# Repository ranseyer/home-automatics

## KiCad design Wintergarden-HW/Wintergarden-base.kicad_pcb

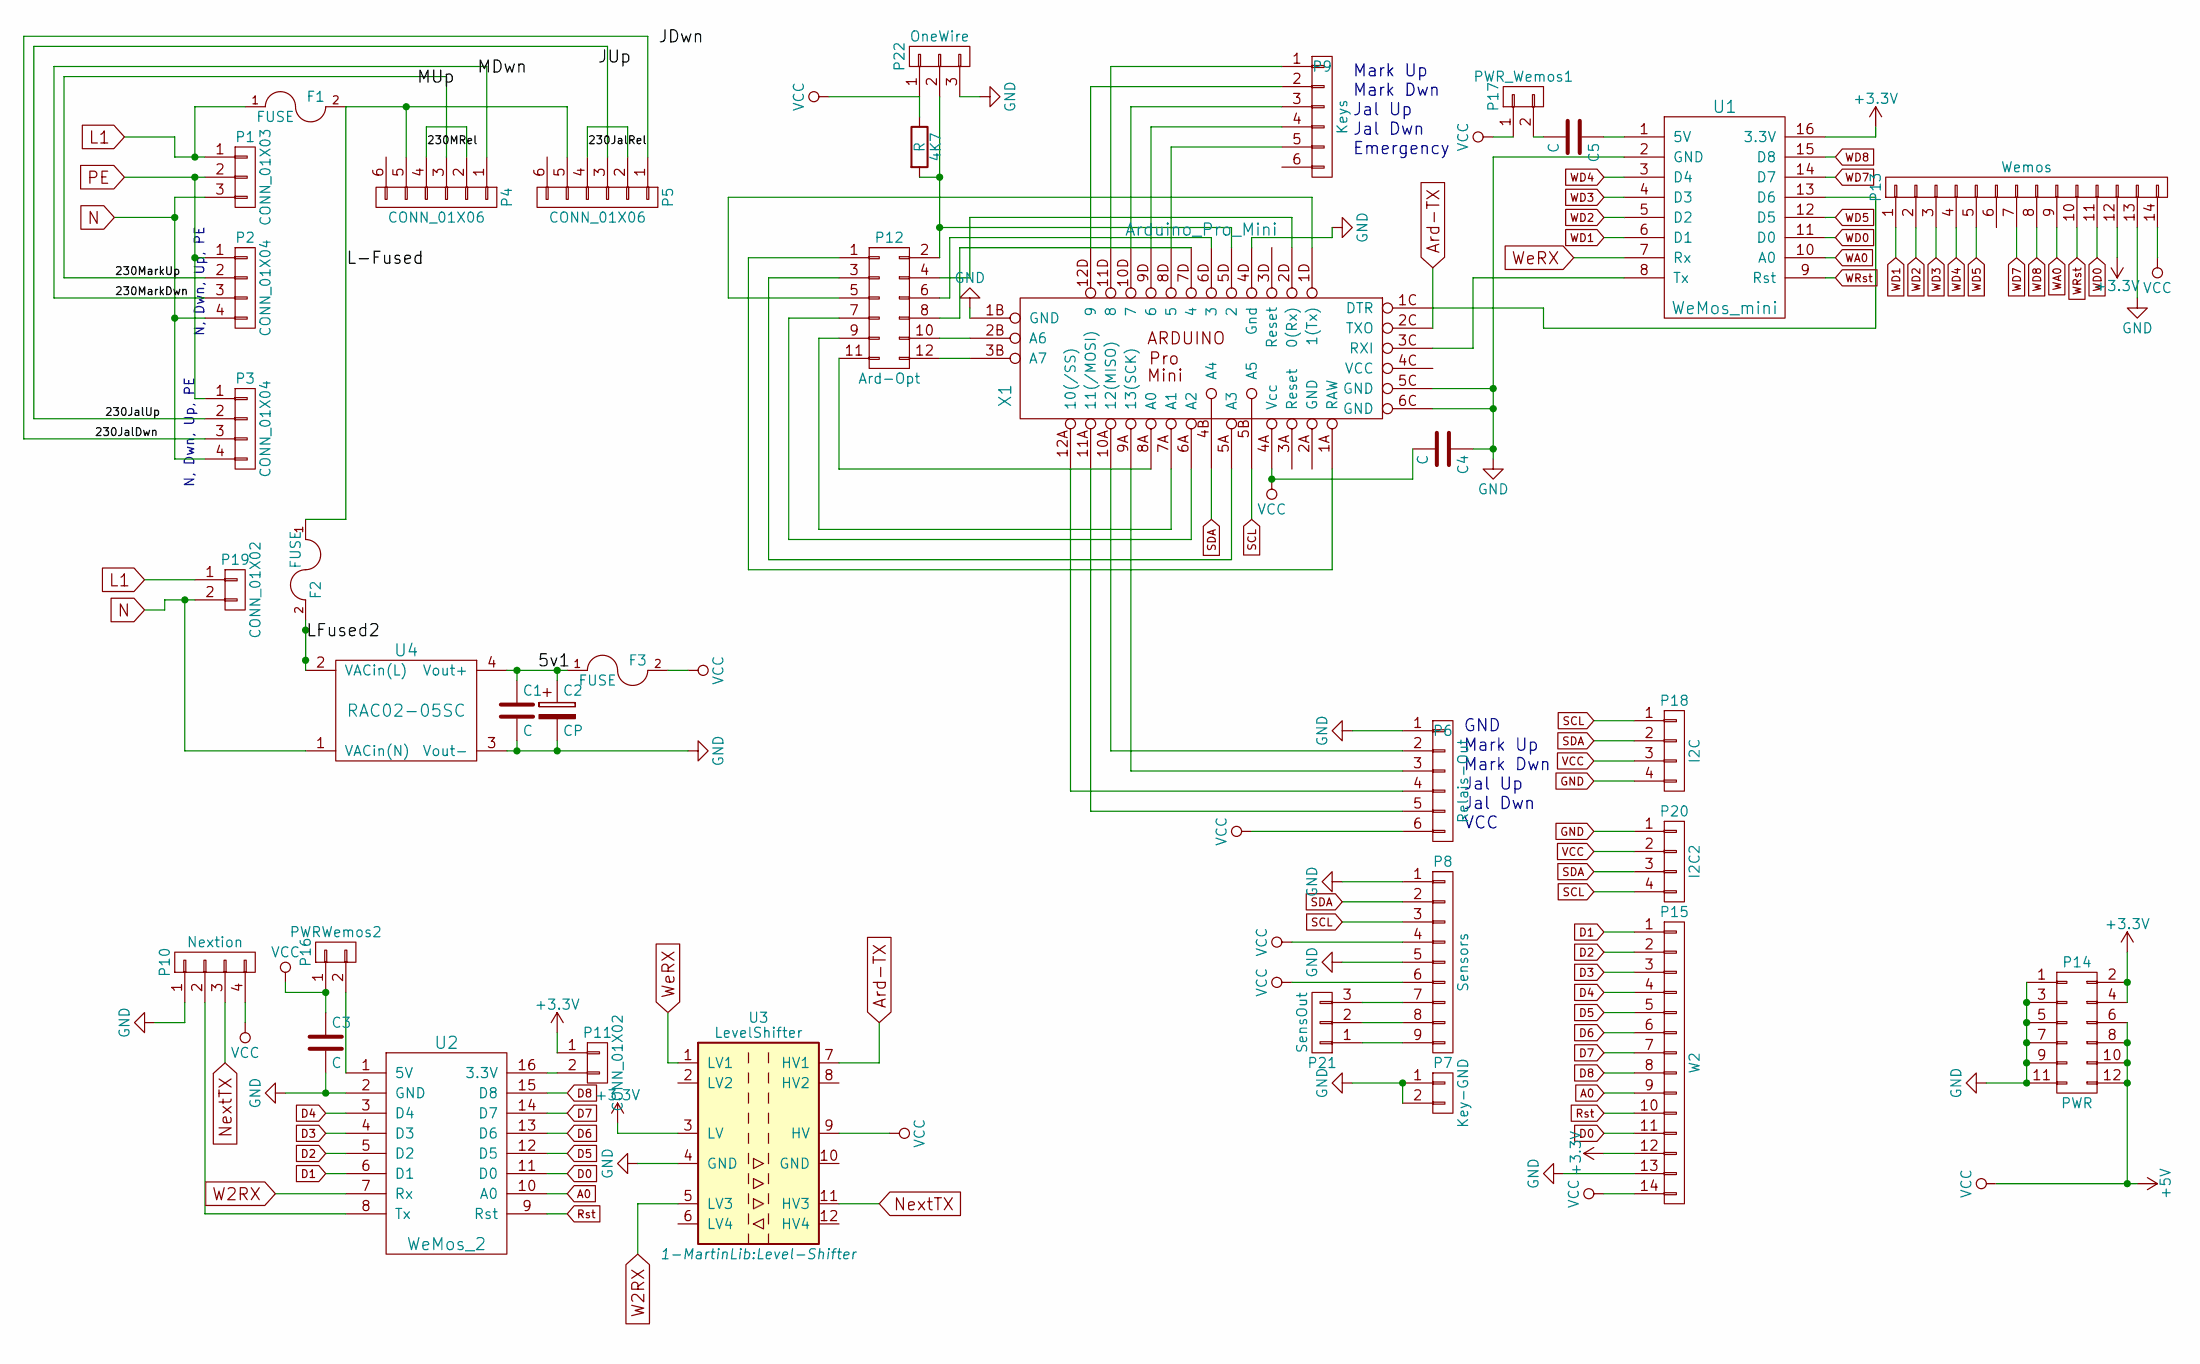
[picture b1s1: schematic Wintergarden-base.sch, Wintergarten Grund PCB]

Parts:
4K7: R; R_0805_HandSoldering
C1: C; C_0805_HandSoldering
C2: CP; C_Radial_D10_L20_P5
C3, C4, C5: C; C_1210_HandSoldering
F1, F2: FUSE; Fuseholder5x20_horiz_SemiClosed_Casing10x25mm
F3: FUSE; Fuseholder_Fuse_TR5_Littlefuse-No560_No460
P1: CONN_01X03; PhoenixContact_MSTBVA-G_03x5.00mm_Vertical
P2, P3: CONN_01X04; PhoenixContact_MSTBVA-G_04x5.00mm_Vertical
P4, P5: CONN_01X06; PhoenixContact_MSTBVA-G_06x5.00mm_Vertical
P6: Relais-Out; Pin_Header_Straight_1x06
P7: Key-GND; PhoenixContact_MSTBVA-G_02x5.00mm_Vertical
P8: Sensors; PhoenixContact_MCV-G_09x3.50mm_Vertical
P9: Keys; PhoenixContact_MCV-G_06x3.50mm_Vertical
P10: Nextion; Pin_Header_Straight_1x04
P11: CONN_01X02; Pin_Header_Straight_2x01
P12: Ard-Opt; Pin_Header_Straight_2x06
P13: Wemos; Pin_Header_Straight_2x07
P14: PWR; Pin_Header_Straight_2x06
P15: W2; Pin_Header_Straight_2x07
P16: PWRWemos2; Pin_Header_Straight_2x01
P17: PWR_Wemos1; Pin_Header_Straight_2x01
P18: I2C; Pin_Header_Straight_1x04
P19: CONN_01X02; PhoenixContact_MSTBVA-G_02x5.00mm_Vertical
P20: I2C2; Pin_Header_Straight_1x04
P21: SensOut; Pin_Header_Straight_1x03
P22: OneWire; Pin_Header_Straight_1x03
U1: WeMos_mini; D1_mini_board
U2: WeMos_2; D1_mini_board
U3: LevelShifter; Level-Shifter
U4: RAC02-05SC; HLK-PM01
X1: Arduino_Pro_Mini

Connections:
+3V3: P11.1, P13.12, P14.2, P14.4, P15.12, U1.16 (3.3V), U3.3 (LV)
/5v1: C1.1, C2.1, F3.1, U4.4 (Vout+)
/230JalDwn: P3.3, P5.1
/230JalRel: P5.2, P5.4
/230JalUp: P3.2, P5.3
/230MRel: P4.2, P4.4
/230MarkDwn: P2.3, P4.1
/230MarkUp: P2.2, P4.3
/L-Fused: F1.2, F2.1, P4.5, P5.5
/LFused2: F2.2, U4.2 (VACin(L))
A0: P15.9, U2.10 (A0)
Ard-TX: U3.7 (HV1), X1.2C (TXO)
D0: P15.11, U2.11 (D0)
D1: P15.1, U2.6 (D1)
D2: P15.2, U2.5 (D2)
D3: P15.3, U2.4 (D3)
D4: P15.4, U2.3 (D4)
D5: P15.5, U2.12 (D5)
D6: P15.6, U2.13 (D6)
D7: P15.7, U2.14 (D7)
D8: P15.8, U2.15 (D8)
GND: C1.2, C2.2, C3.2, C4.1, P6.1, P7.1, P7.2, P8.1, P8.5, P10.1, P13.13, P14.1, P14.3, P14.5, P14.7, P14.9, P14.11, P15.13, P18.4, P20.1, P22.3, U1.2 (GND), U2.2 (GND), U3.4 (GND), U4.3 (Vout-), X1.1B (GND), X1.4D (Gnd), X1.5C (GND), X1.6C (GND)
L1: F1.1, P1.1, P19.1
N: P1.3, P2.4, P3.4, P19.2, U4.1 (VACin(N))
unnamed: 4K7.2, P12.2, P22.2, X1.5D (2)
unnamed: C5.1, U1.1 (5V)
unnamed: C5.2, P17.2
unnamed: P6.2, X1.10A (12(MISO))
unnamed: P6.3, X1.9A (13(SCK))
unnamed: P6.4, X1.12A (10(/SS))
unnamed: P6.5, X1.11A (11(/MOSI))
unnamed: P9.1, X1.11D (8)
unnamed: P9.2, X1.12D (9)
unnamed: P9.3, X1.10D (7)
unnamed: P9.4, X1.9D (6)
unnamed: P9.5, X1.8D (5)
unnamed: P10.2, U2.8 (Tx)
unnamed: P11.2, U2.16 (3.3V)
unnamed: P12.1, X1.1A (RAW)
unnamed: P12.3, X1.5A (A3)
unnamed: P12.4, X1.2D (0(Rx))
unnamed: P12.5, X1.1D (1(Tx))
unnamed: P12.6, X1.6D (3)
unnamed: P12.7, X1.6A (A2)
unnamed: P12.8, X1.7D (4)
unnamed: P12.9, X1.7A (A1)
unnamed: P12.10, X1.2B (A6)
unnamed: P12.11, X1.8A (A0)
unnamed: P12.12, X1.3B (A7)
unnamed: P16.2, U2.1 (5V)
unnamed: P8.9, P21.1
unnamed: P8.8, P21.2
unnamed: P8.7, P21.3
unnamed: U1.8 (Tx), X1.3C (RXI)
unnamed: U1.13 (D6), X1.1C (DTR)
NextTX: P10.3, U3.11 (HV3)
PE: P1.2, P2.1, P3.1
Rst: P15.10, U2.9 (Rst)
SCL: P8.3, P18.1, P20.4, X1.5B (A5)
SDA: P8.2, P18.2, P20.3, X1.4B (A4)
VCC: 4K7.1, C3.1, C4.2, F3.2, P6.6, P8.4, P8.6, P10.4, P13.14, P14.6, P14.8, P14.10, P14.12, P15.14, P16.1, P17.1, P18.3, P20.2, P22.1, U3.9 (HV), X1.4A (Vcc)
W2RX: U2.7 (Rx), U3.5 (LV3)
WA0: P13.9, U1.10 (A0)
WD0: P13.11, U1.11 (D0)
WD1: P13.1, U1.6 (D1)
WD2: P13.2, U1.5 (D2)
WD3: P13.3, U1.4 (D3)
WD4: P13.4, U1.3 (D4)
WD5: P13.5, U1.12 (D5)
WD7: P13.7, U1.14 (D7)
WD8: P13.8, U1.15 (D8)
WRst: P13.10, U1.9 (Rst)
WeRX: U1.7 (Rx), U3.1 (LV1)

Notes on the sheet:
N, Dwn, Up, PE
GND Mark Up Mark Dwn Jal Up Jal Dwn VCC
Mark Up Mark Dwn Jal Up Jal Dwn Emergency

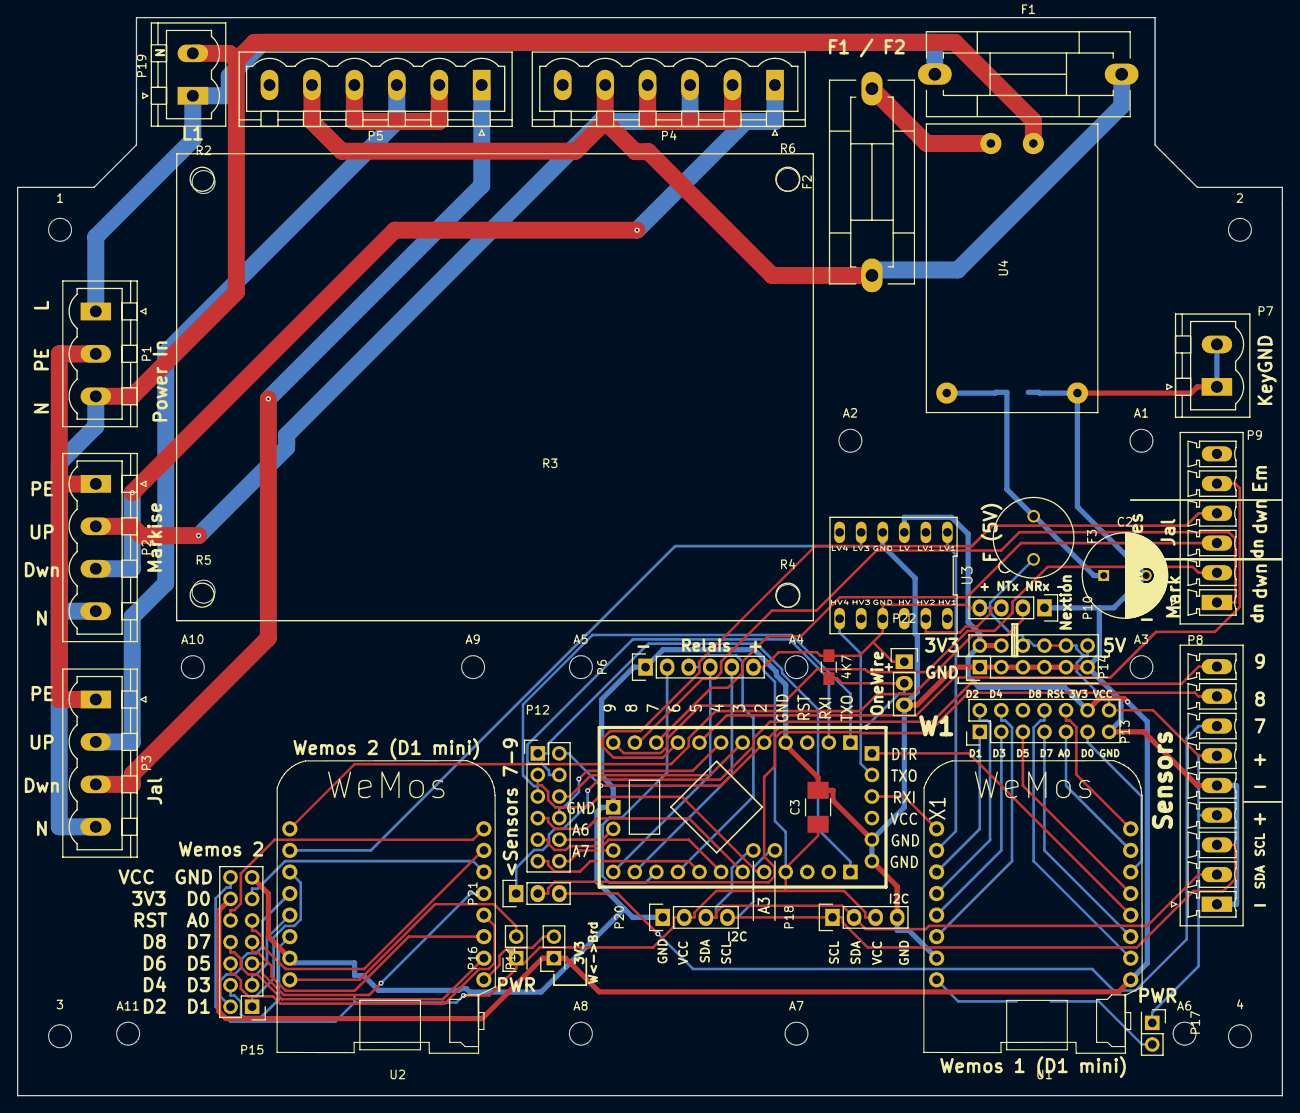
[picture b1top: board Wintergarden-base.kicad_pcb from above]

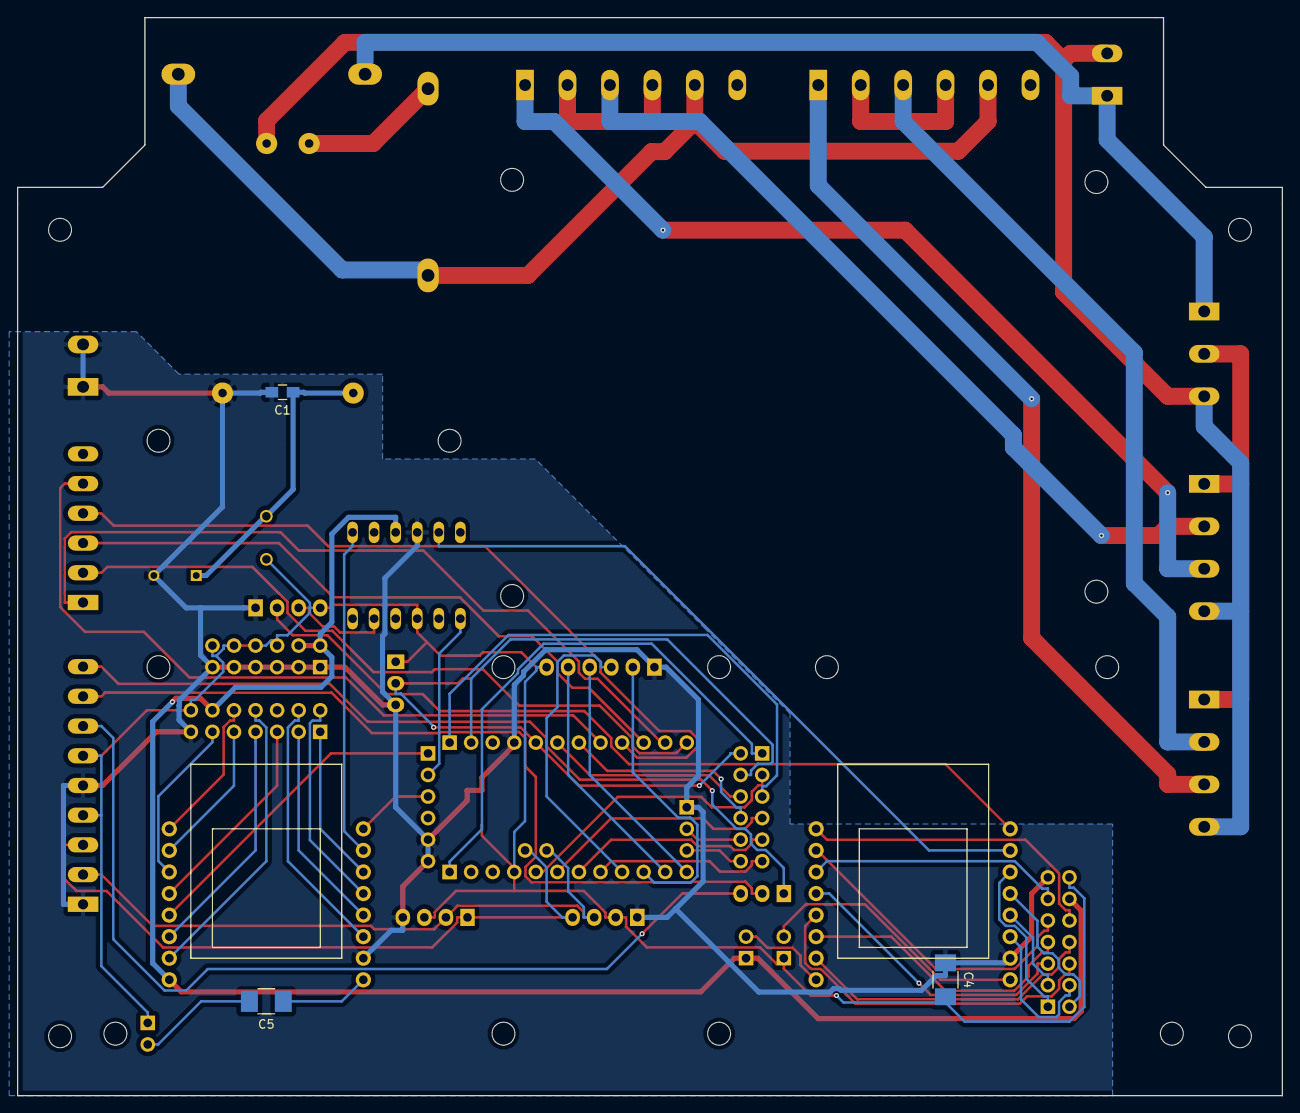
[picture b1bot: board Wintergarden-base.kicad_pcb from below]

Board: 2 copper layers, 149.0 x 127.0 mm, 56 parts (3 on the bottom side), 73 nets.

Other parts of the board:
1, 2, 3, 4: MountingHole_2.7mm_M2.5
A1, A2, A3, A4, A5, A6, A7, A8, A9, A10, A11: MountingHole_2.7mm_M2.5_ISO14580
R2, R4, R5, R6: MountingHole_2.7mm_M2.5
R3: Relais-Board-4x

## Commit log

2016-04-29 nanoCUL works
2016-04-29 Serial GW (mySensors)
2016-05-11 Wettersensor
2016-08-23 RGBWW
2016-09-18 H801 Sming-Test1
2016-09-18 H801 Readme
2016-10-15 Wintergarden-HW with own libs for levelshifter and 4xrelaisboard footprint
2016-10-26 MySenS GW2
2016-11-23 Nextion Display
2016-12-03 ESP-Link
2016-12-20 Doku
2017-01-04 H801 RGBWW Light
2017-02-15 Adapter Lvl Shifter
2017-02-15 Cleanup
2017-02-16 MySensors easyRS485
2017-02-24 MySensors easyRS485 Image-Exports
2017-03-05 MySensors easyRS485 V2
2017-04-14 Mains Voltage-Sensor
2017-05-12 MySens Gateways
2017-05-31 Rain-Sensors + some RS485 Boards
2017-06-17 Rain-Sensor: Calculation of the heating
2017-06-17 Rain-Sensor: Images
2017-06-29 Rain-Sensor: little fix
2017-07-08 Rain-Sensor: little fixes
2017-07-08 Rollershutter Test
2017-07-08 Rollershutter Test2
2017-07-28 MySysNanoGW-Node + Rain UweH
2017-08-22 MySens easy ProMini
2017-08-25 MySens easyProMini -Draft2
2017-08-29 MySens V01 (ordered)
2017-08-29 readme
2017-08-29 readme2
2017-08-29 More docu
2017-10-17 Some new easyBoards
2017-10-18 little fixes for new easyBoards
2017-10-31 MySensors moved to a new repo
2017-12-29 RS485 Termination
2017-12-29 Update RS485 Termin
2017-12-29 Rs485 Term
2017-12-29 rs485 Terminator update
2018-01-01 Rain Doku
2018-01-02 BOM Rainsensor
2018-01-28 Ambiligh-Levelshifter + LEDE Rectifier
2018-02-17 RFID Lock
    initial
2018-02-17 Lock
    Value in String
2018-02-17 Lock
    RS485
2018-02-17 Lock
    Presentation
2018-02-17 Lock
2018-02-28 test
2018-03-03 RFID Initial
2018-03-03 rfid
2018-03-03 rfid
    Found tag id: 0xF6,0xEA,0x25,0x3B,0x00,0x00,0x00
    Start
    0x246,0x234,0x37,0x59,0x00,0x00,0x00
    Ende
2018-03-04 rfid
    works but uggly
2018-03-04 rfid
    input von Betauser
2018-03-04 RFID OK without local Keys
2018-03-20 RFID-Lock works
2018-11-17 Zigbee Schematic Export
2018-11-17 Little fix
2018-12-05 Zigbee V02
2018-12-20 Deloghi Images
2018-12-27 url
    url
2019-04-29 Rain SW
2019-05-05 Water Sendsor
2019-05-06 Water-Sensor V01
2019-05-12 cc2530
2019-06-22 docu 1w water-sens
2019-11-08 Homematic-Wintergarten / WiFi Candle
2021-01-20 Power Supply + Cleanup
2021-01-29 WLED + HMModUART-CP2102
2021-02-15 pics
2021-04-12 Cleanup Homematic
